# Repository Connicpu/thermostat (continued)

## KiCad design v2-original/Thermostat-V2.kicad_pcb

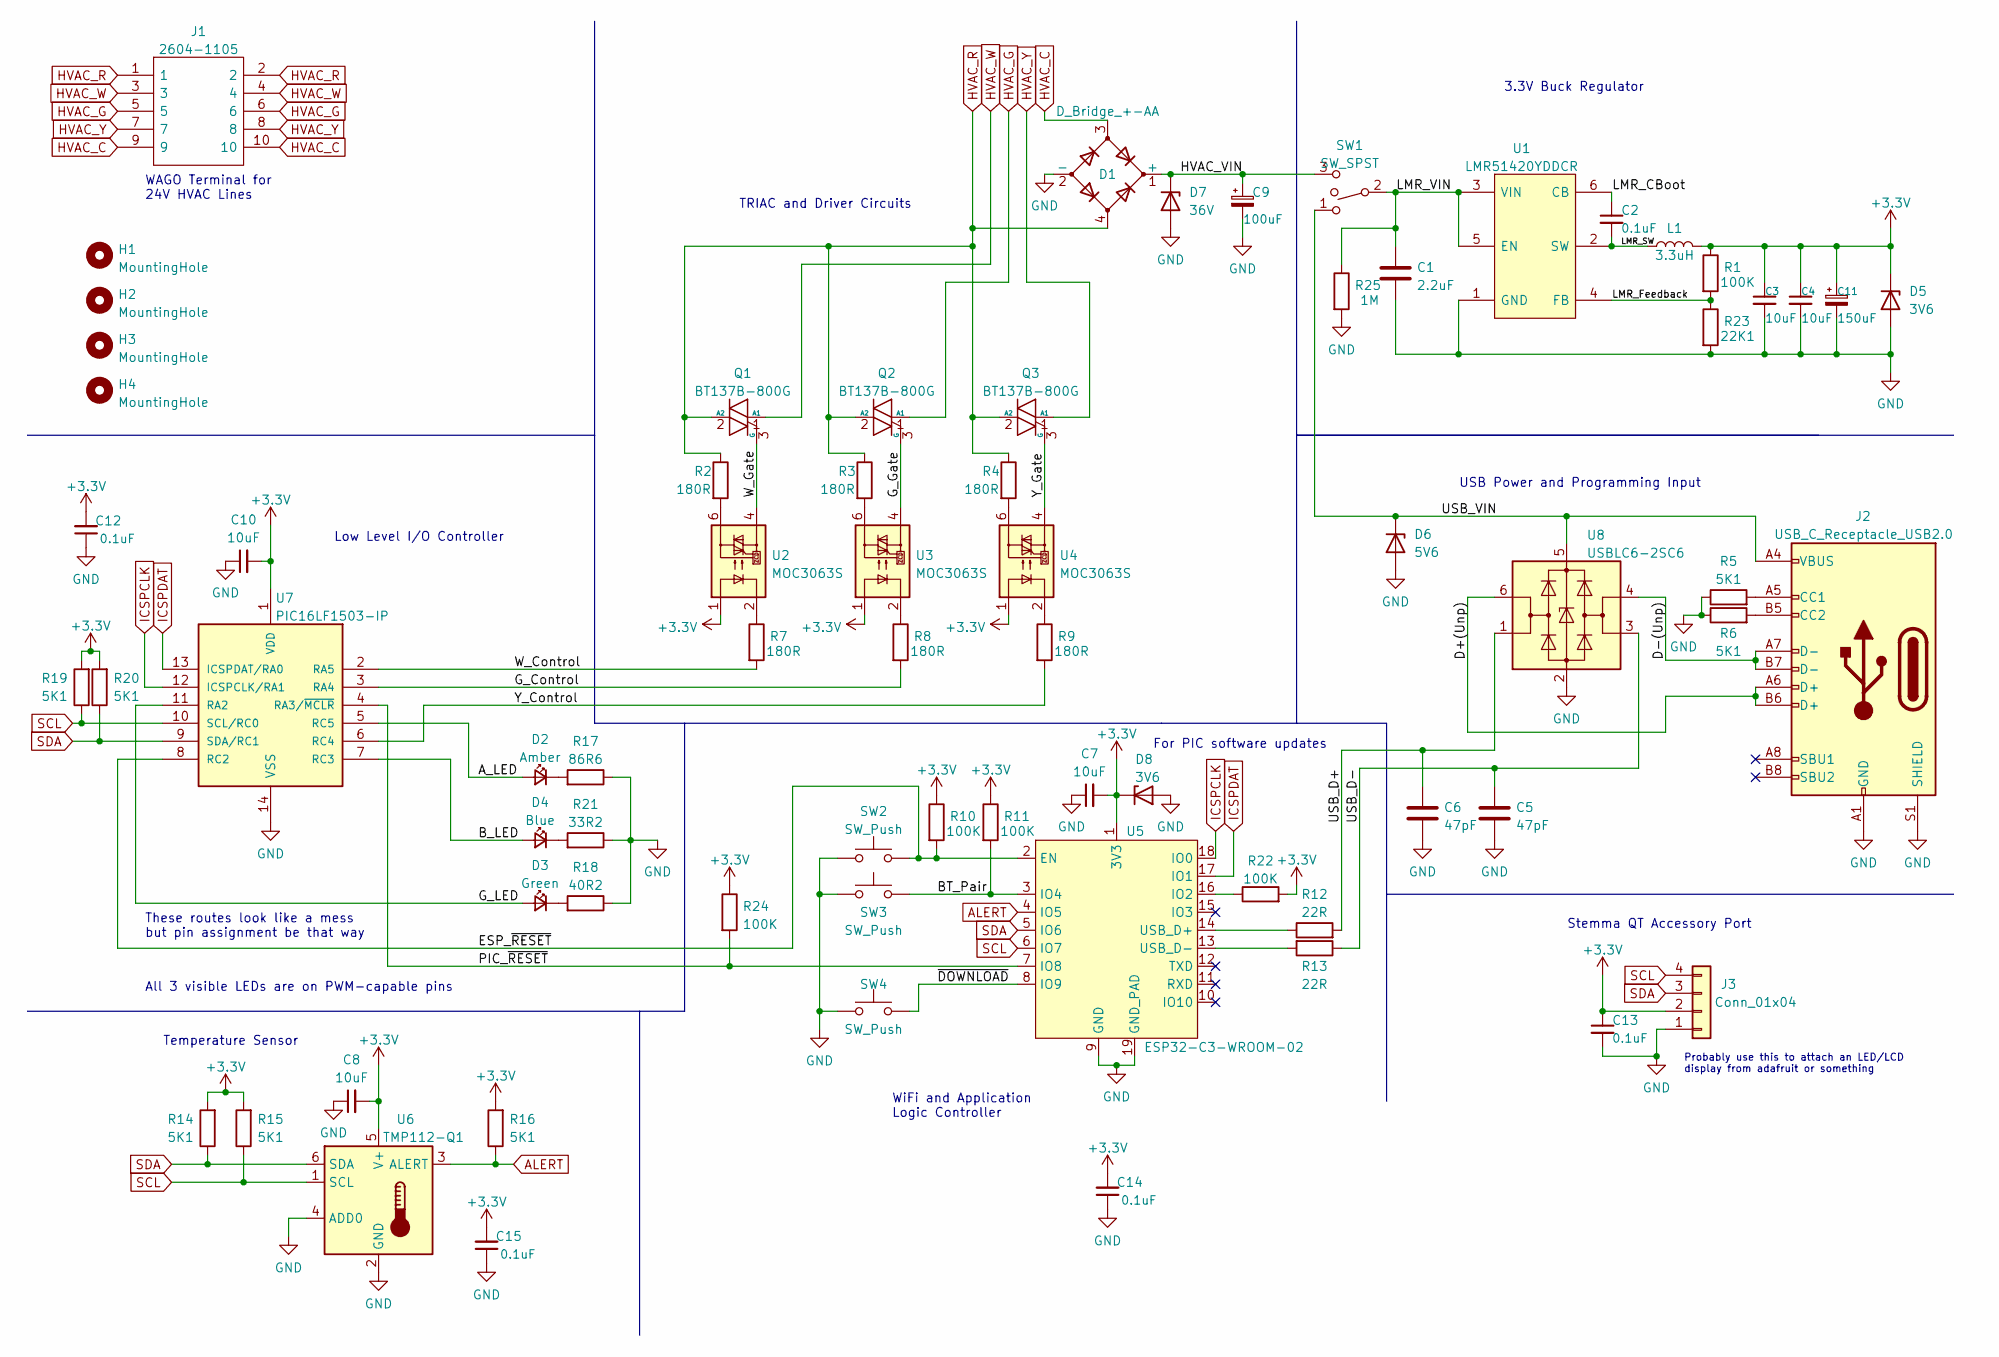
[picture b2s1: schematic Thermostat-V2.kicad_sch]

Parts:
C1: 2.2uF; C_0603_1608Metric_Pad1.08x0.95mm_HandSolder
C2, C12, C13, C14, C15: 0.1uF; C_0402_1005Metric_Pad0.74x0.62mm_HandSolder
C3, C4, C7, C8, C10: 10uF; C_0805_2012Metric_Pad1.18x1.45mm_HandSolder
C5, C6: 47pF; C_0402_1005Metric_Pad0.74x0.62mm_HandSolder
C9: 100uF; CP_Elec_8x6.9
C11: 150uF; CP_Elec_8x6.9
D1: D_Bridge_+-AA; Diode_Bridge_Diotec_ABS
D2: Amber; D_0603_1608Metric_Pad1.05x0.95mm_HandSolder
D3: Green; D_0603_1608Metric_Pad1.05x0.95mm_HandSolder
D4: Blue; D_0603_1608Metric_Pad1.05x0.95mm_HandSolder
D5, D8: 3V6; SOT-23_Handsoldering
D6: 5V6; SOT-23_Handsoldering
D7: 36V; SOT-23_Handsoldering
H1, H2, H3, H4: MountingHole; MountingHole_4.3mm_M4
J1: 2604-1105; 26041105; Manufacturer_Part_Number 2604-1105
J2: USB_C_Receptacle_USB2.0; USB_C_Receptacle_HRO_TYPE-C-31-M-12
J3: Conn_01x04; JST_SH_SM04B-SRSS-TB_1x04-1MP_P1.00mm_Horizontal
L1: 3.3uH; L_1210_3225Metric_Pad1.42x2.65mm_HandSolder
Q1, Q2, Q3: BT137B-800G; TO-263-2
R1, R10, R11, R22, R24: 100K; R_0201_0603Metric_Pad0.64x0.40mm_HandSolder
R2, R3, R4, R7, R8, R9: 180R; R_0402_1005Metric_Pad0.72x0.64mm_HandSolder
R5, R6, R14, R15, R16, R19, R20: 5K1; R_0402_1005Metric_Pad0.72x0.64mm_HandSolder
R12, R13: 22R; R_0201_0603Metric_Pad0.64x0.40mm_HandSolder
R17: 86R6; R_0402_1005Metric_Pad0.72x0.64mm_HandSolder
R18: 40R2; R_0402_1005Metric_Pad0.72x0.64mm_HandSolder
R21: 33R2; R_0402_1005Metric_Pad0.72x0.64mm_HandSolder
R23: 22K1; R_0402_1005Metric_Pad0.72x0.64mm_HandSolder
R25: 1M; R_0402_1005Metric_Pad0.72x0.64mm_HandSolder
SW1: SW_SPST; 500SSP3S1M6QEA
SW2, SW3, SW4: SW_Push; SW_PUSH_6mm
U1: LMR51420YDDCR; SOP95P280X110-6N; Manufacturer_Part_Number LMR51420YDDCR
U2, U3, U4: MOC3063S; SMDIP-6_W7.62mm
U5: ESP32-C3-WROOM-02; ESP32C3WROOM02N4
U6: TMP112-Q1; SOT-563
U7: PIC16LF1503-IP; DIP-14_W7.62mm_Socket
U8: USBLC6-2SC6; SOT-23-6

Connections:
+3V3: C3.1, C4.1, C7.2, C8.2, C10.2, C11.1, C12.2, C13.1, C14.2, C15.2, D5.3 (K), D8.3 (K), J3.2, L1.2, R1.1, R10.1, R11.1, R14.2, R15.2, R16.2, R19.2, R20.2, R22.2, R24.1, U2.1, U3.1, U4.1, U5.1 (3V3), U6.5 (V+), U7.1 (VDD)
/A_LED: D2.2 (A), U7.5 (RC5)
/BT_Pair: R11.2, SW3.2, U5.3 (IO4)
/B_LED: D4.2 (A), U7.7 (RC3)
/D+(Unp): J2.A6 (D+), J2.B6 (D+), U8.6 (I/O1)
/D-(Unp): J2.A7 (D-), J2.B7 (D-), U8.4 (I/O2)
/ESP_~RESET: R10.2, SW2.2, U5.2 (EN), U7.8 (RC2)
/G_Control: R8.2, U7.3 (RA4)
/G_Gate: Q2.3 (G), U3.4
/G_LED: D3.2 (A), U7.11 (RA2)
/HVAC_VIN: C9.1, D1.1 (+), D7.3 (K), SW1.3
/LMR_CBoot: C2.1, U1.6 (CB)
/LMR_Feedback: R1.2, R23.1, U1.4 (FB)
/LMR_SW: C2.2, L1.1, U1.2 (SW)
/LMR_VIN: C1.1, R25.1, SW1.2, U1.3 (VIN), U1.5 (EN)
/PIC_~RESET: R24.2, U5.7 (IO8), U7.4 (RA3/~MCLR)
/USB_D+: C6.2, R12.2, U8.1 (I/O1)
/USB_D-: C5.1, R13.1, U8.3 (I/O2)
/USB_VIN: D6.3 (K), J2.A4 (VBUS), J2.A9 (VBUS), J2.B4 (VBUS), J2.B9 (VBUS), SW1.1, U8.5 (VBUS)
/W_Control: R7.2, U7.2 (RA5)
/W_Gate: Q1.3 (G), U2.4
/Y_Control: R9.2, U7.6 (RC4)
/Y_Gate: Q3.3 (G), U4.4
/~DOWNLOAD: SW4.2, U5.8 (IO9)
ALERT: R16.1, U5.4 (IO5), U6.3 (ALERT)
GND: C1.2, C3.2, C4.2, C5.2, C6.1, C7.1, C8.1, C9.2, C10.1, C11.2, C12.1, C13.2, C14.1, C15.1, D1.2 (-), D5.1 (A), D6.1 (A), D7.1 (A), D8.1 (A), J2.A1 (GND), J2.A12 (GND), J2.B1 (GND), J2.B12 (GND), J2.S1 (SHIELD), J3.1, R5.1, R6.1, R17.1, R18.1, R21.1, R23.2, R25.2, SW2.1, SW3.1, SW4.1, U1.1 (GND), U5.9 (GND), U5.19 (GND_PAD), U6.2 (GND), U6.4 (ADD0), U7.14 (VSS), U8.2 (GND)
HVAC_C: D1.3, J1.9, J1.10
HVAC_G: J1.5, J1.6, Q2.1 (A1)
HVAC_R: D1.4, J1.1, J1.2, Q1.2 (A2), Q2.2 (A2), Q3.2 (A2), R2.1, R3.1, R4.1
HVAC_W: J1.3, J1.4, Q1.1 (A1)
HVAC_Y: J1.7, J1.8, Q3.1 (A1)
ICSPCLK: U5.18 (IO0), U7.12 (ICSPCLK/RA1)
ICSPDAT: U5.17 (IO1), U7.13 (ICSPDAT/RA0)
unnamed: D2.1 (K), R17.2
unnamed: D3.1 (K), R18.2
unnamed: D4.1 (K), R21.2
unnamed: J2.A5 (CC1), R5.2
unnamed: J2.B5 (CC2), R6.2
unnamed: R2.2, U2.6
unnamed: R3.2, U3.6
unnamed: R4.2, U4.6
unnamed: R7.1, U2.2
unnamed: R8.1, U3.2
unnamed: R9.1, U4.2
unnamed: R12.1, U5.14 (USB_D+)
unnamed: R13.2, U5.13 (USB_D-)
unnamed: R22.1, U5.16 (IO2)
SCL: J3.4, R15.1, R19.1, U5.6 (IO7), U6.1 (SCL), U7.10 (SCL/RC0)
SDA: J3.3, R14.1, R20.1, U5.5 (IO6), U6.6 (SDA), U7.9 (SDA/RC1)

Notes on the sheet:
Stemma QT Accessory Port
Low Level I/O Controller
Temperature Sensor
These routes look like a mess but pin assignment be that way
All 3 visible LEDs are on PWM-capable pins
USB Power and Programming Input
WAGO Terminal for 24V HVAC Lines
WiFi and Application Logic Controller
Probably use this to attach an LED/LCD display from adafruit or something
3.3V Buck Regulator
For PIC software updates
TRIAC and Driver Circuits

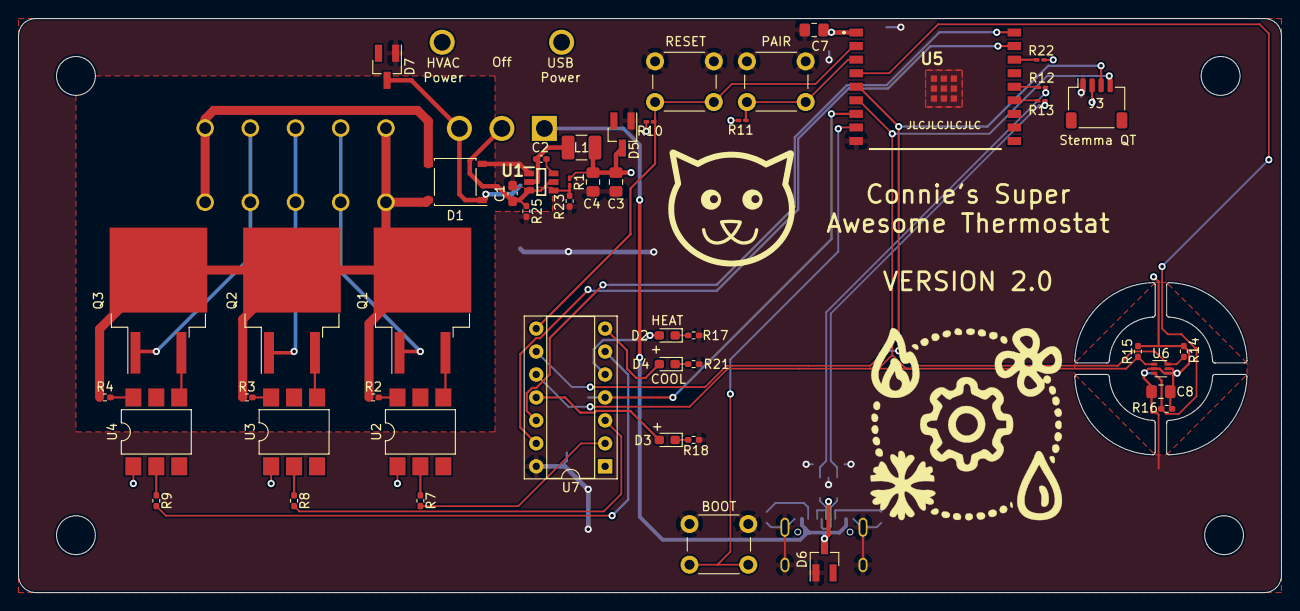
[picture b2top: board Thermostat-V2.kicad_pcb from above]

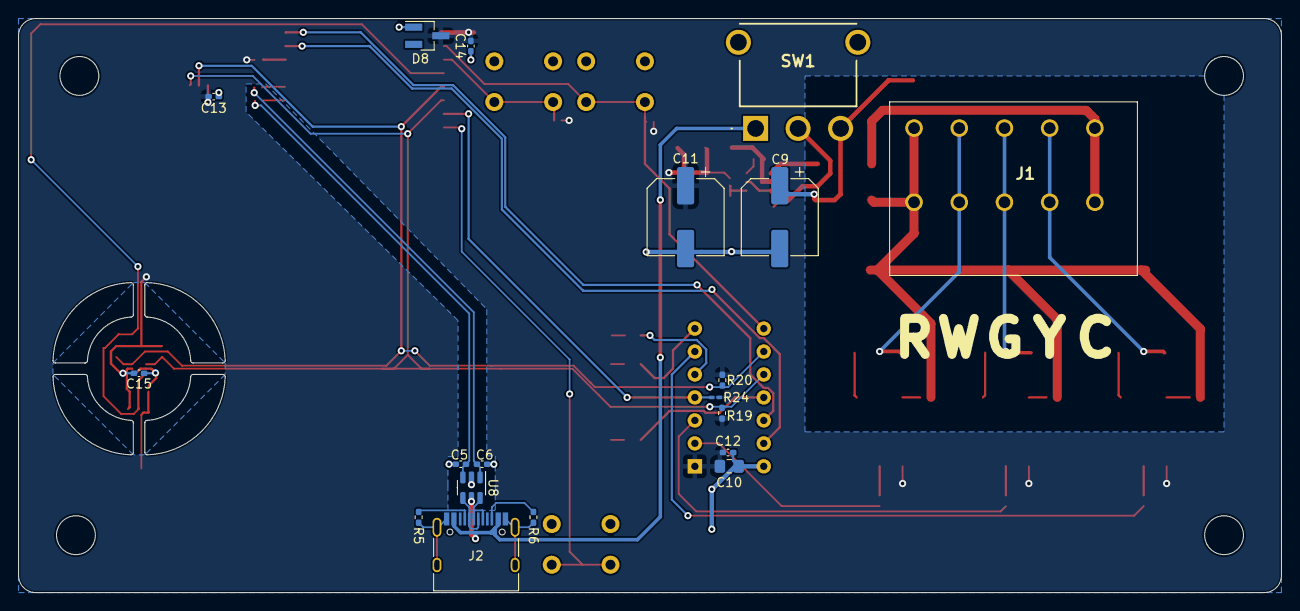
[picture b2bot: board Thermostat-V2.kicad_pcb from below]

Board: 2 copper layers, 139.7 x 63.5 mm, 71 parts (19 on the bottom side), 49 nets.
